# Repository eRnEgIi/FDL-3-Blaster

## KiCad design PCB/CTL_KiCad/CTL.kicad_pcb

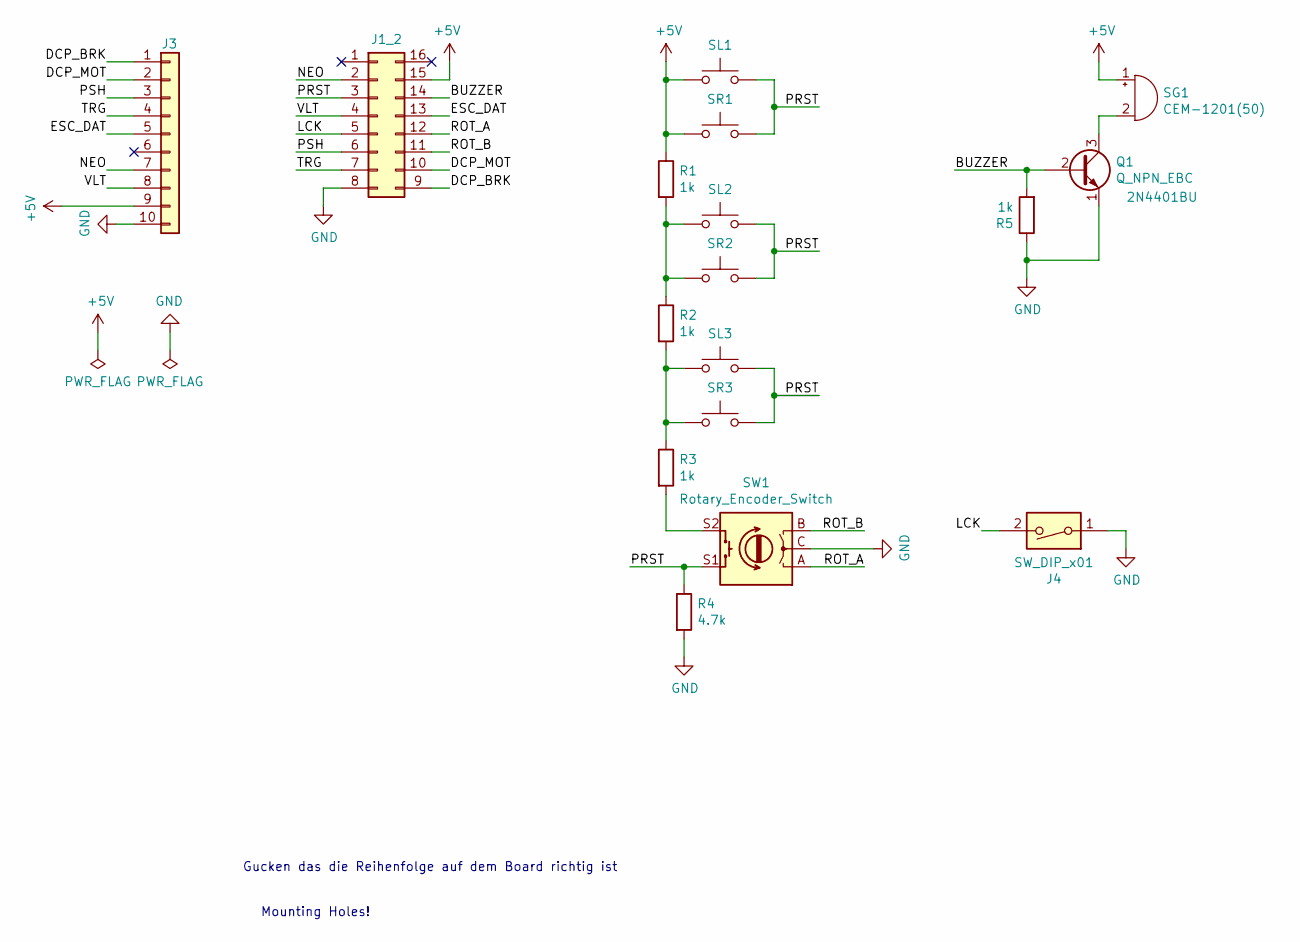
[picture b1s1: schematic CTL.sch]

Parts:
J1_2: Conn_02x08_Counter_Clockwise; MicroVIew
J3: Conn_01x10; PinHeader_1x10_P2.54mm_Vertical
J4: SW_DIP_x01; SW_DIP_SPSTx01_Slide_6.7x4.1mm_W7.62mm_P2.54mm_LowProfile
Q1: Q_NPN_EBC; TO-92; DigiKey 2N4401BU
R1, R2, R3, R5: 1k; R_Axial_DIN0204_L3.6mm_D1.6mm_P5.08mm_Horizontal
R4: 4.7k; R_Axial_DIN0204_L3.6mm_D1.6mm_P5.08mm_Horizontal
SG1: CEM-1201(50); DigiKey 102-1152-ND
SL1, SL2, SL3: SW_Push; SW_Tactile_SPST_Angled_PTS645Vx31-2LFS
SR1, SR2, SR3: SW_Push; SW_Tactile_SPST_Angled_PTS645Vx31-2LFS
SW1: Rotary_Encoder_Switch; PEC11R-4215K-S0024

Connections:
+5V: J1_2.15, J3.9, R1.1, SG1.1 (-), SL1.1, SR1.1
/BUZZER: J1_2.14, Q1.2 (B), R5.2
/DCP_BRK: J1_2.9, J3.1
/DCP_MOT: J1_2.10, J3.2
/ESC_DAT: J1_2.13, J3.5
/LCK: J1_2.5, J4.2
/NEO: J1_2.2, J3.7
/PRST: J1_2.3, R4.1, SL1.2, SL2.2, SL3.2, SR1.2, SR2.2, SR3.2, SW1.S1
/PSH: J1_2.6, J3.3
/ROT_A: J1_2.12, SW1.A
/ROT_B: J1_2.11, SW1.B
/TRG: J1_2.7, J3.4
/VLT: J1_2.4, J3.8
GND: J1_2.8, J3.10, J4.1, Q1.1 (E), R4.2, R5.1, SW1.C
unnamed: Q1.3 (C), SG1.2 (+)
unnamed: R1.2, R2.1, SL2.1, SR2.1
unnamed: R2.2, R3.1, SL3.1, SR3.1
unnamed: R3.2, SW1.S2

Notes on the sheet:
Gucken das die Reihenfolge auf dem Board richtig ist
Mounting Holes!

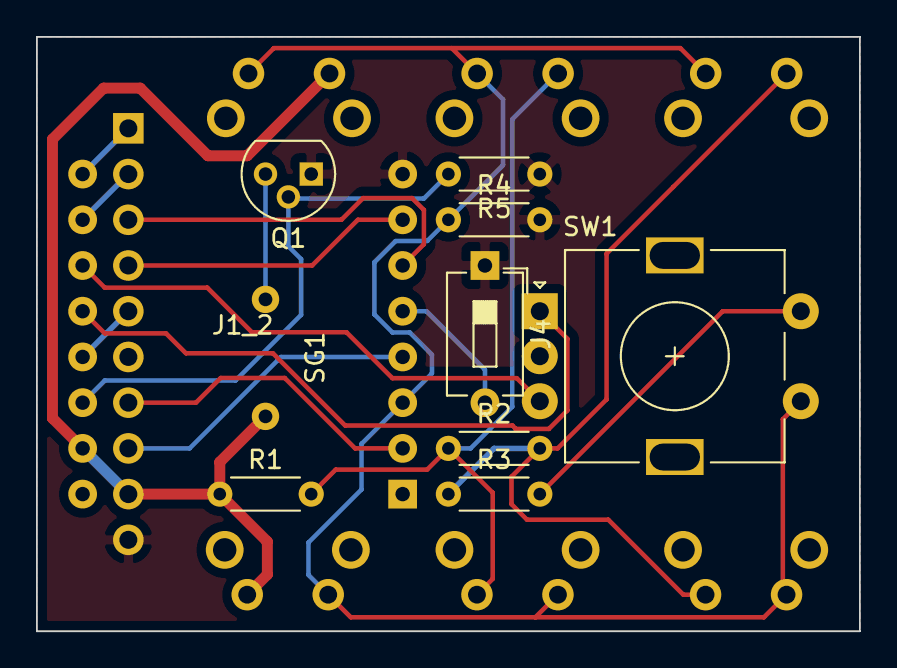
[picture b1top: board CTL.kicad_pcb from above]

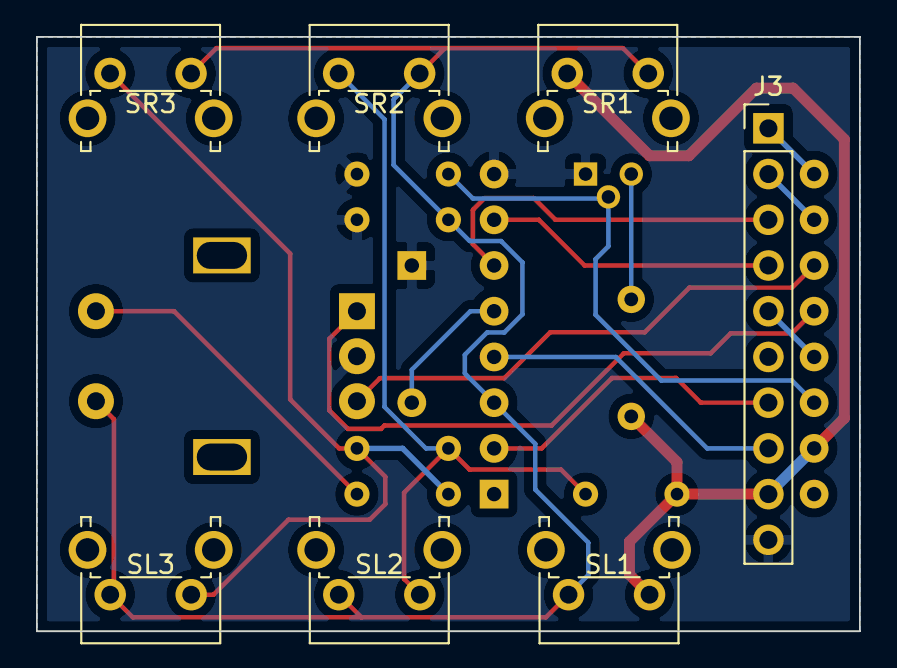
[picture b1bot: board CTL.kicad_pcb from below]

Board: 2 copper layers, 45.7 x 33.0 mm, 17 parts (7 on the bottom side), 18 nets.

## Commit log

2020-11-28 Recreated schematic from eagle with KiCad. Set some parts.
2020-11-29 Initial Version of KiCAD based CTL board.
